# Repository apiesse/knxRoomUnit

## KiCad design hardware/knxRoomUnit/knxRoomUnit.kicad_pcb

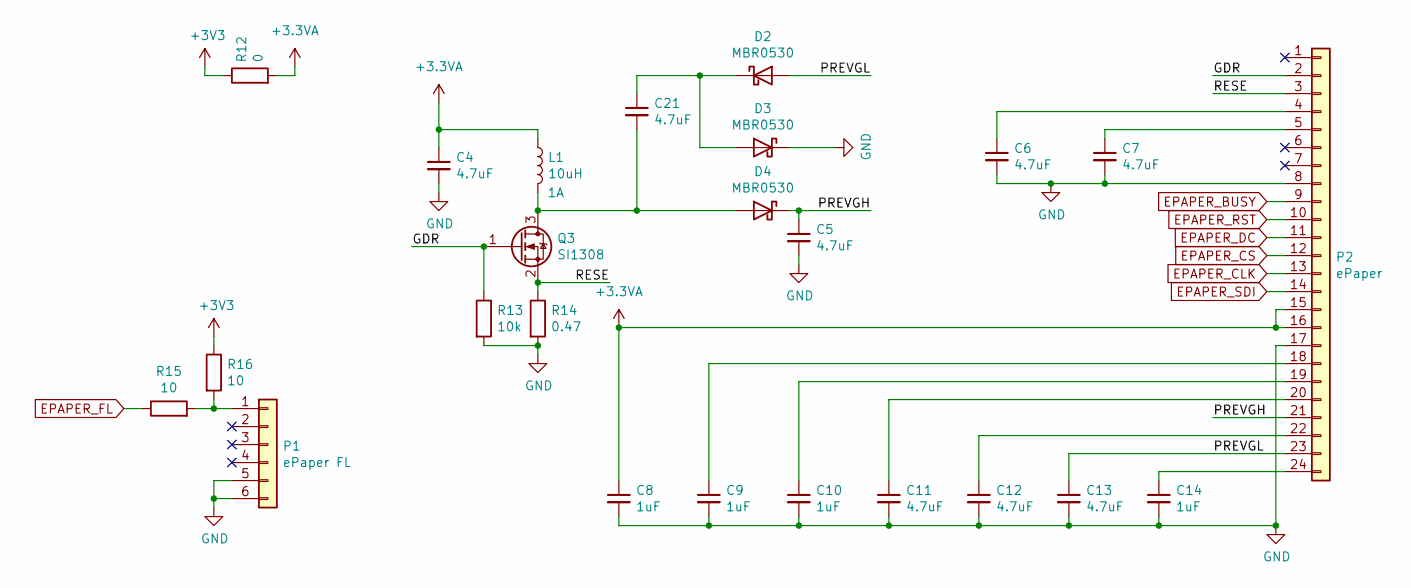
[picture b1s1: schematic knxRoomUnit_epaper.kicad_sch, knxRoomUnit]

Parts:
C4, C5, C6, C7, C11, C12, C13, C21: 4.7uF; C_0603_1608Metric; Voltage 16V; PartNumber CL10A475KO8NNNC; LCSC Part # C19666
C8, C9, C10, C14: 1uF; C_0603_1608Metric; Voltage 50V; PartNumber CL10A105KB8NNNC; LCSC Part # C15849
D2, D3, D4: MBR0530; D_SOD-123; PartNumber MBR0530; LCSC Part # C5204746
L1: 10uH; L_Wuerth_MAPI-3020; Voltage 1A; PartNumber XFL3012-103MEC
P1: ePaper FL; Hirose_FH12-6S-0.5SH_1x06-1MP_P0.50mm_Horizontal; PartNumber AFC34-S06FIA-00; LCSC Part # C2842522
P2: ePaper; Hirose_FH12-24S-0.5SH_1x24-1MP_P0.50mm_Horizontal; PartNumber AFC34-S24FIA-00; LCSC Part # C2842527
Q3: SI1308; SOT-323_SC-70; PartNumber SI1308EDL-T1-GE3; LCSC Part # C469327
R12: 0; R_0805_2012Metric; PartNumber 0805W8F0000T5E; LCSC Part # C17477
R13: 10k; R_0603_1608Metric; PartNumber 0603WAF1002T5E; LCSC Part # C25804
R14: 0.47; R_0603_1608Metric
R15: 10; R_0805_2012Metric; PartNumber 0805W8F100JT5E; LCSC Part # C17415
R16: 10; R_0805_2012Metric; PartNumber 0805W8J0100T5E; LCSC Part # C25278

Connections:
+3.3VA: C4.1, C8.1, L1.1, P2.15, P2.16, R12.2
/ePaper/GDR: P2.2, Q3.1 (G), R13.1
/ePaper/PREVGH: C5.1, D4.1 (K), P2.21
/ePaper/PREVGL: C13.1, D2.2 (A), P2.23
/ePaper/RESE: P2.3, Q3.2 (S), R14.1
EPAPER_BUSY: P2.9; also elsewhere on the board
EPAPER_CLK: P2.13; also elsewhere on the board
EPAPER_CS: P2.12; also elsewhere on the board
EPAPER_DC: P2.11; also elsewhere on the board
EPAPER_FL: R15.1; also elsewhere on the board
EPAPER_RST: P2.10; also elsewhere on the board
EPAPER_SDI: P2.14; also elsewhere on the board
GND: C4.2, C5.2, C6.2, C7.2, C8.2, C9.2, C10.2, C11.2, C12.2, C13.2, C14.2, D3.1 (K), P1.5, P1.6, P2.8, P2.17, R13.2, R14.2; also elsewhere on the board
unnamed: C21.1, D2.1 (K), D3.2 (A)
unnamed: C21.2, D4.2 (A), L1.2, Q3.3 (D)
unnamed: P1.1, R15.2, R16.2
unnamed: C6.1, P2.4
unnamed: C7.1, P2.5
unnamed: C9.1, P2.18
unnamed: C10.1, P2.19
unnamed: C11.1, P2.20
unnamed: C12.1, P2.22
unnamed: C14.1, P2.24

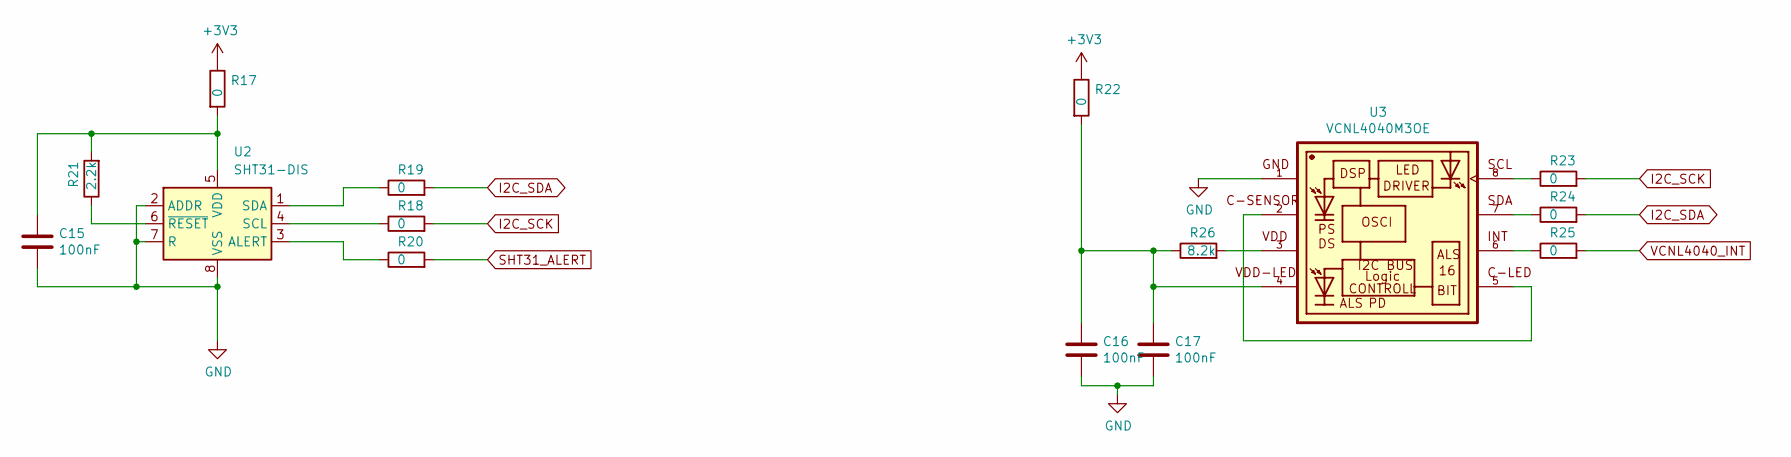
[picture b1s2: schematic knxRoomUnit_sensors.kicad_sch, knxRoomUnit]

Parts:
C15, C16, C17: 100nF; C_0603_1608Metric; Voltage 50V; PartNumber CC0603KRX7R9BB104; LCSC Part # C14663
R17, R18, R19, R20, R22, R23, R24, R25: 0; R_0603_1608Metric; PartNumber 0603WAF0000T5E; LCSC Part # C21189
R21: 2.2k; R_0603_1608Metric; PartNumber 0603WAF2201T5E; LCSC Part # C4190
R26: 8.2k; R_0603_1608Metric; PartNumber 0603WAF8201T5E; LCSC Part # C25981
U2: SHT31-DIS; Sensirion_DFN-8-1EP_2.5x2.5mm_P0.5mm_EP1.1x1.7mm; PartNumber SHT31-DIS-B2.5kS; LCSC Part # C80862
U3: VCNL4040M3OE; VISHAY_VCNL4040_4X2X1.1; PartNumber VCNL4040M3OE; LCSC Part # C142526

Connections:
GND: C15.2, C16.2, C17.2, U2.2 (ADDR), U2.7 (R), U2.8 (VSS), U2.9 (VSS), U3.1; also elsewhere on the board
I2C_SCK: R18.2, R23.2; also elsewhere on the board
I2C_SDA: R19.2, R24.2; also elsewhere on the board
unnamed: C16.1, C17.1, R22.2, R26.1, U3.4
unnamed: R23.1, U3.8
unnamed: R24.1, U3.7
unnamed: R25.1, U3.6
unnamed: R26.2, U3.3
unnamed: R20.1, U2.3 (ALERT)
unnamed: R18.1, U2.4 (SCL)
unnamed: R19.1, U2.1 (SDA)
unnamed: C15.1, R17.2, R21.2, U2.5 (VDD)
unnamed: R21.1, U2.6 (~RESET)
unnamed: U3.2, U3.5
SHT31_ALERT: R20.2; also elsewhere on the board
VCNL4040_INT: R25.2; also elsewhere on the board

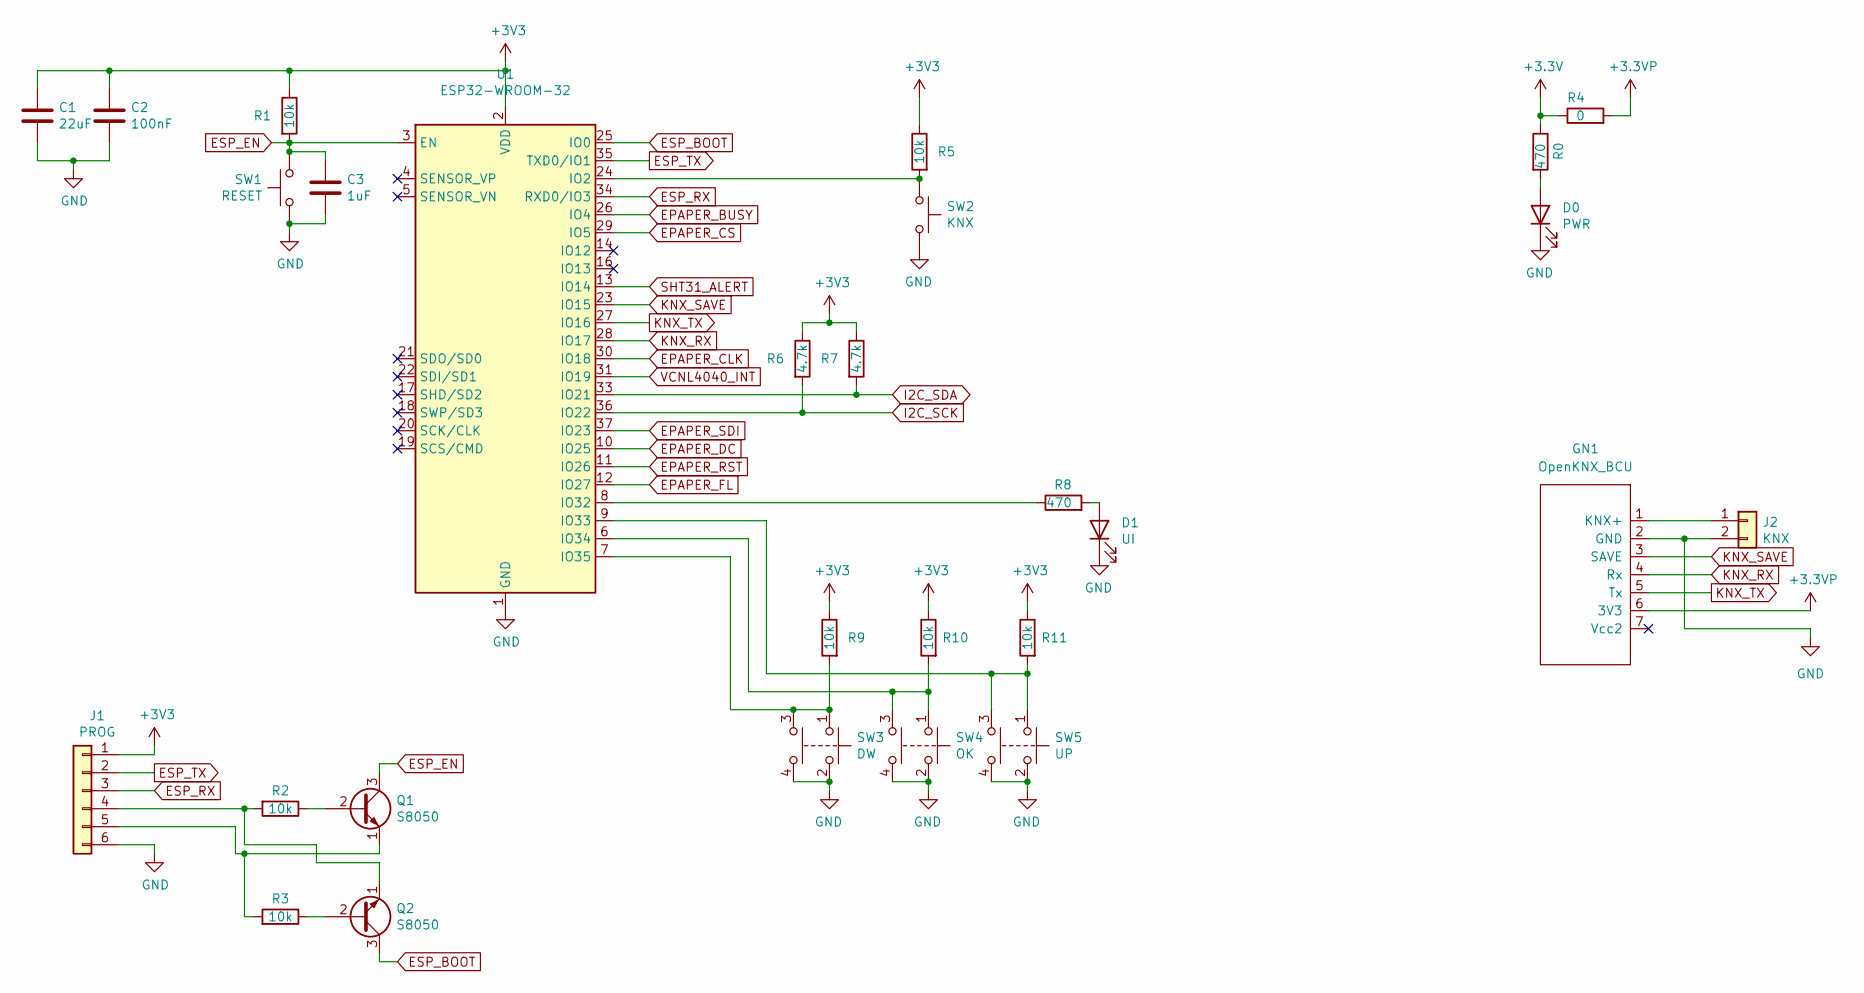
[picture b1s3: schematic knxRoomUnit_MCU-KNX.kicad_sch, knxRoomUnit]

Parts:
C1: 22uF; C_0603_1608Metric; Voltage 6.3V; PartNumber CL10A226MQ8NRNC; LCSC Part # C59461
C2: 100nF; C_0603_1608Metric; Voltage 50V; PartNumber CC0603KRX7R9BB104; LCSC Part # C14663
C3: 1uF; C_0603_1608Metric; Voltage 50V; PartNumber CL10A105KB8NNNC; LCSC Part # C15849
D0: PWR; LED_0603_1608Metric_Pad1.05x0.95mm_HandSolder
D1: UI; LED_0603_1608Metric_Pad1.05x0.95mm_HandSolder
GN1: OpenKNX_BCU; NanoBCU_PinHeader_SMD_low_profile
J1: PROG; PinHeader_1x06_P2.54mm_Vertical
J2: KNX; KNX_Connector
Q1, Q2: S8050; SOT-23; PartNumber SS8050; LCSC Part # C2150
R0, R8: 470; R_0603_1608Metric; PartNumber 0603WAF4700T5E; LCSC Part # C23179
R1, R2, R3, R5, R9, R10, R11: 10k; R_0603_1608Metric; PartNumber 0603WAF1002T5E; LCSC Part # C25804
R4: 0; R_0805_2012Metric; PartNumber 0805W8F0000T5E; LCSC Part # C17477
R6, R7: 4.7k; R_0603_1608Metric; PartNumber 0603WAF4701T5E; LCSC Part # C23162
SW1: RESET; SW_Push_SPST_NO_Alps_SKRK
SW2: KNX; SW_Push_SPST_NO_Alps_SKRK
SW3: DW; 431151008826; PartNumber 431151008826
SW4: OK; 431151008826; PartNumber 431151008826
SW5: UP; 431151008826; PartNumber 431151008826
U1: ESP32-WROOM-32; PartNumber ESP32-WROOM-32E

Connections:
+3.3VP: GN1.6 (3V3), R4.2
EPAPER_BUSY: U1.26 (IO4); also elsewhere on the board
EPAPER_CLK: U1.30 (IO18); also elsewhere on the board
EPAPER_CS: U1.29 (IO5); also elsewhere on the board
EPAPER_DC: U1.10 (IO25); also elsewhere on the board
EPAPER_FL: U1.12 (IO27); also elsewhere on the board
EPAPER_RST: U1.11 (IO26); also elsewhere on the board
EPAPER_SDI: U1.37 (IO23); also elsewhere on the board
ESP_BOOT: Q2.3 (C), U1.25 (IO0)
ESP_EN: C3.1, Q1.3 (C), R1.2, SW1.1, U1.3 (EN)
ESP_RX: J1.3, U1.34 (RXD0/IO3)
ESP_TX: J1.2, U1.35 (TXD0/IO1)
GND: C1.2, C2.2, C3.2, D0.1 (K), D1.1 (K), GN1.2 (GND), J1.6, J2.2, SW1.2, SW2.2, SW3.2, SW3.4, SW4.2, SW4.4, SW5.2, SW5.4, U1.1 (GND), U1.15 (GND), U1.38 (GND), U1.39 (GND); also elsewhere on the board
I2C_SCK: R6.2, U1.36 (IO22); also elsewhere on the board
I2C_SDA: R7.2, U1.33 (IO21); also elsewhere on the board
KNX_RX: GN1.4 (Rx), U1.28 (IO17)
KNX_SAVE: GN1.3 (SAVE), U1.23 (IO15)
KNX_TX: GN1.5 (Tx), U1.27 (IO16)
unnamed: D0.2 (A), R0.2
unnamed: D1.2 (A), R8.2
unnamed: GN1.1 (KNX+), J2.1
unnamed: J1.4, Q2.1 (E), R2.2
unnamed: J1.5, Q1.1 (E), R3.2
unnamed: Q1.2 (B), R2.1
unnamed: Q2.2 (B), R3.1
unnamed: R5.2, SW2.1, U1.24 (IO2)
unnamed: R8.1, U1.8 (IO32)
unnamed: R11.2, SW5.1, SW5.3, U1.9 (IO33)
unnamed: R10.2, SW4.1, SW4.3, U1.6 (IO34)
unnamed: R9.2, SW3.1, SW3.3, U1.7 (IO35)
SHT31_ALERT: U1.13 (IO14); also elsewhere on the board
VCNL4040_INT: U1.31 (IO19); also elsewhere on the board

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
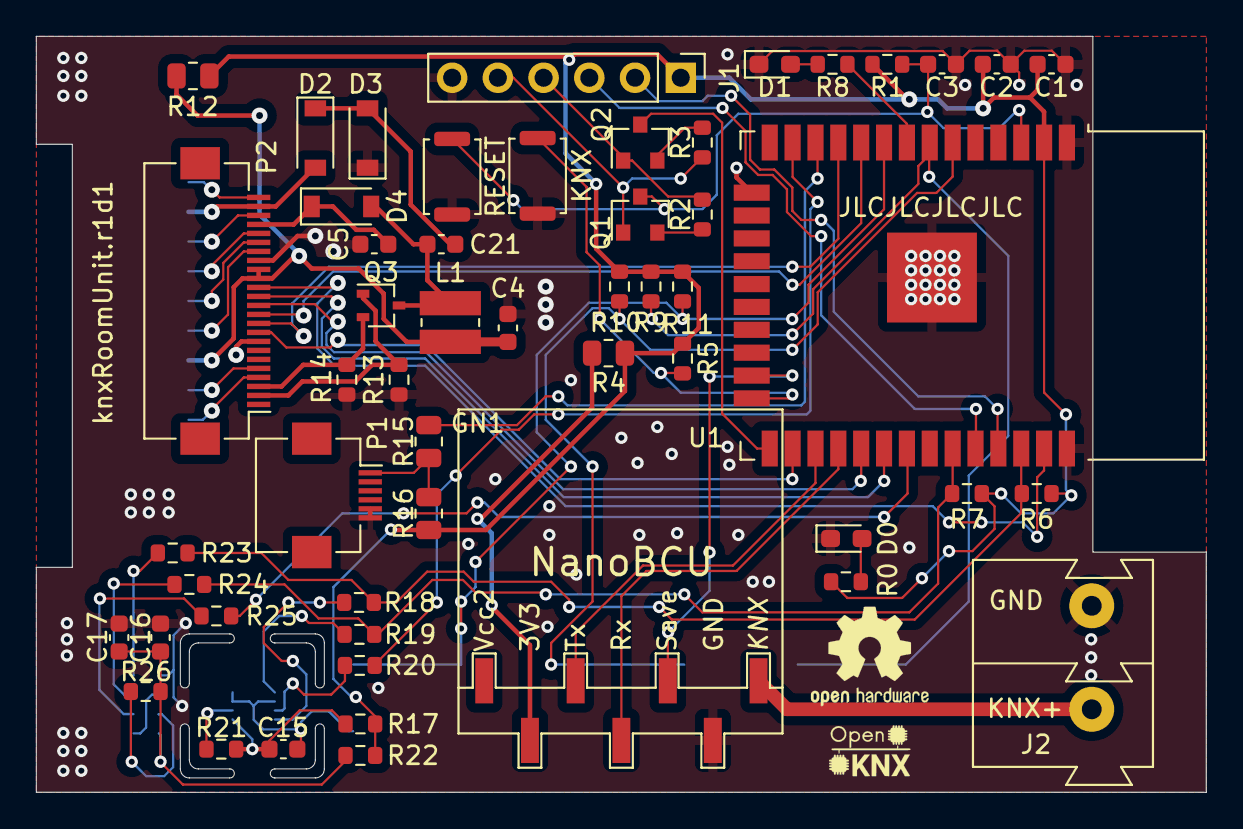
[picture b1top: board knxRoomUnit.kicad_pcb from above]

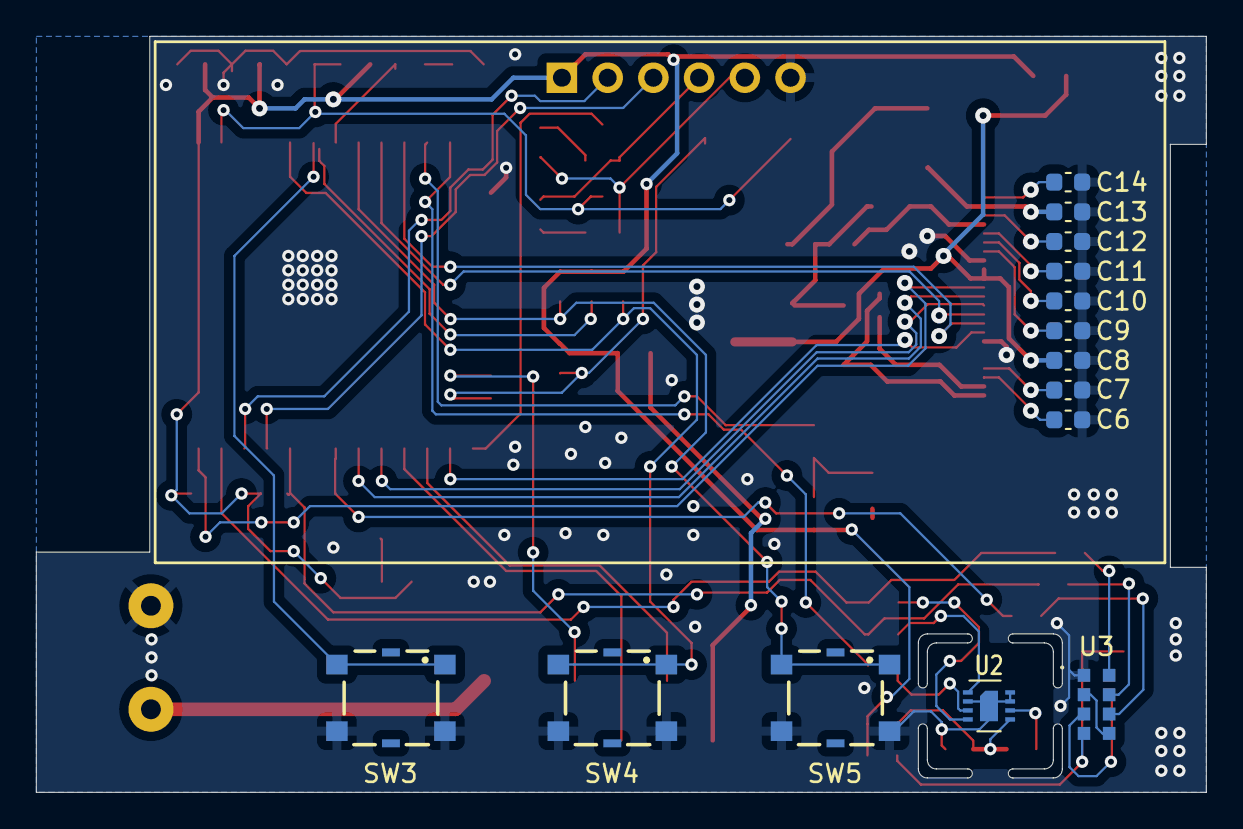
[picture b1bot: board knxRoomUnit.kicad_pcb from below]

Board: 2 copper layers, 65.0 x 42.0 mm, 67 parts (14 on the bottom side), 59 nets.

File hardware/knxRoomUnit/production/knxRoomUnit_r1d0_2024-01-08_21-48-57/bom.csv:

Designator,Footprint,Quantity,Value,LCSC Part #
C1,0603,1,22uF,C59461
"C10, C14, C3, C8, C9",0603,5,1uF,C15849
"C11, C12, C13, C21, C4, C5, C6, C7",0603,8,4.7uF,C19666
"C15, C16, C17, C2",0603,4,100nF,C14663
"D2, D3, D4",D_SOD-123,3,MBR0530,C5204746
"Q1, Q2",SOT-23,2,S8050,C2150
Q3,SOT-323_SC-70,1,SI1308,C469327
"R0, R8",0603,2,75,C21189
"R1, R10, R11, R13, R2, R3, R5, R9",0603,8,10k,C25804
"R12, R4",0805,2,0,C17477
R14,0603,1,0.47,
R15,0805,1,10,C25278
"R17, R18, R19, R20, R22, R23, R24, R25",0201,8,0,C21189
R21,0603,1,2.2k,C4190
R26,0603,1,8.2k,C25981
"R6, R7",0603,2,4.7k,C23162
U2,Sensirion_DFN-8-1EP_2.5x2.5mm_P0.5mm_EP1.1x1.7mm,1,SHT31-DIS,C80862
U3,VISHAY_VCNL4040_4X2X1.1,1,VCNL4040M3OE,C142526

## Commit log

2022-01-04 KnxRoomUnit hardware
    Added KnxRoomUnit hardware repository
2023-08-22 Initial hardware commit
2023-08-22 Hardware Update
2023-08-22 Create fp-info-cache
2023-08-22 Added VCNL4040 Kicad library
2023-08-22 Updated sensors
2024-01-03 Update OpenKNX-KiCad-Lib
    Updated OpenKNX-KiCad-Lib
2024-01-03 PCB routing
2024-01-05 Added WE431151008826 models
2024-01-05 Finished PCB routing
2024-01-07 Production adjustments
2024-01-07 Added HW production files
2024-01-08 Fixed directory structure
2024-01-08 Fixed HW production files
2024-01-21 Updated HW design
    Flipped P1 to match display's pinout
    Changed 0201 resistors to 0603
    Added R12 to section 3V3 to display
2024-01-23 Updated HW design
    Changed R0/R8 to 470R
    PCB routing and DRC
